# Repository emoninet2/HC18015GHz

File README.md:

# HC18015GHz
-3dB 180 degrees hybrid coupler in 65nm CMOS

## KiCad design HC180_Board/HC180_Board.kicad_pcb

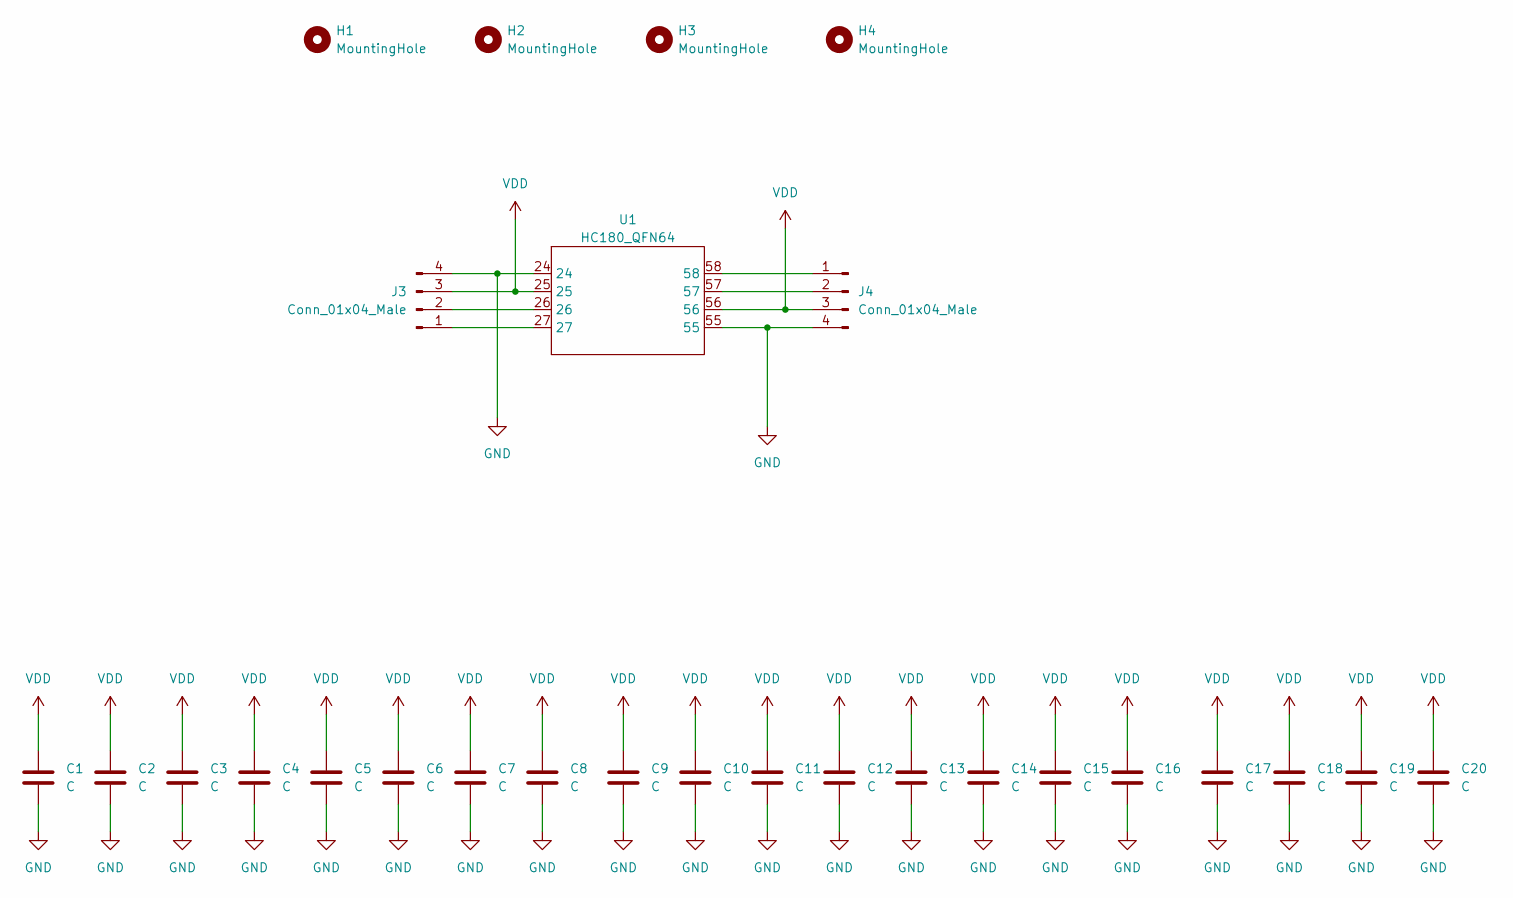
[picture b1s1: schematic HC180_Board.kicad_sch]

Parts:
C1, C2, C3, C4, C5, C6, C7, C8, C9, C10, C11, C12, C13, C14, C15, C16, C17, C18, C19, C20: C; C_0805_2012Metric
H1, H2, H3, H4: MountingHole; MountingHole_5mm_Pad
J3, J4: Conn_01x04_Male; PinHeader_1x04_P2.54mm_Horizontal
U1: HC180_QFN64; QFN-64-1EP_9x9mm_P0.5mm_EP6x6mm

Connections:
GND: C1.2, C2.2, C3.2, C4.2, C5.2, C6.2, C7.2, C8.2, C9.2, C10.2, C11.2, C12.2, C13.2, C14.2, C15.2, C16.2, C17.2, C18.2, C19.2, C20.2, J3.4, J4.4, U1.24, U1.55
unnamed: J3.1, U1.27
unnamed: J3.2, U1.26
unnamed: J4.1, U1.58
unnamed: J4.2, U1.57
VDD: C1.1, C2.1, C3.1, C4.1, C5.1, C6.1, C7.1, C8.1, C9.1, C10.1, C11.1, C12.1, C13.1, C14.1, C15.1, C16.1, C17.1, C18.1, C19.1, C20.1, J3.3, J4.3, U1.25, U1.56

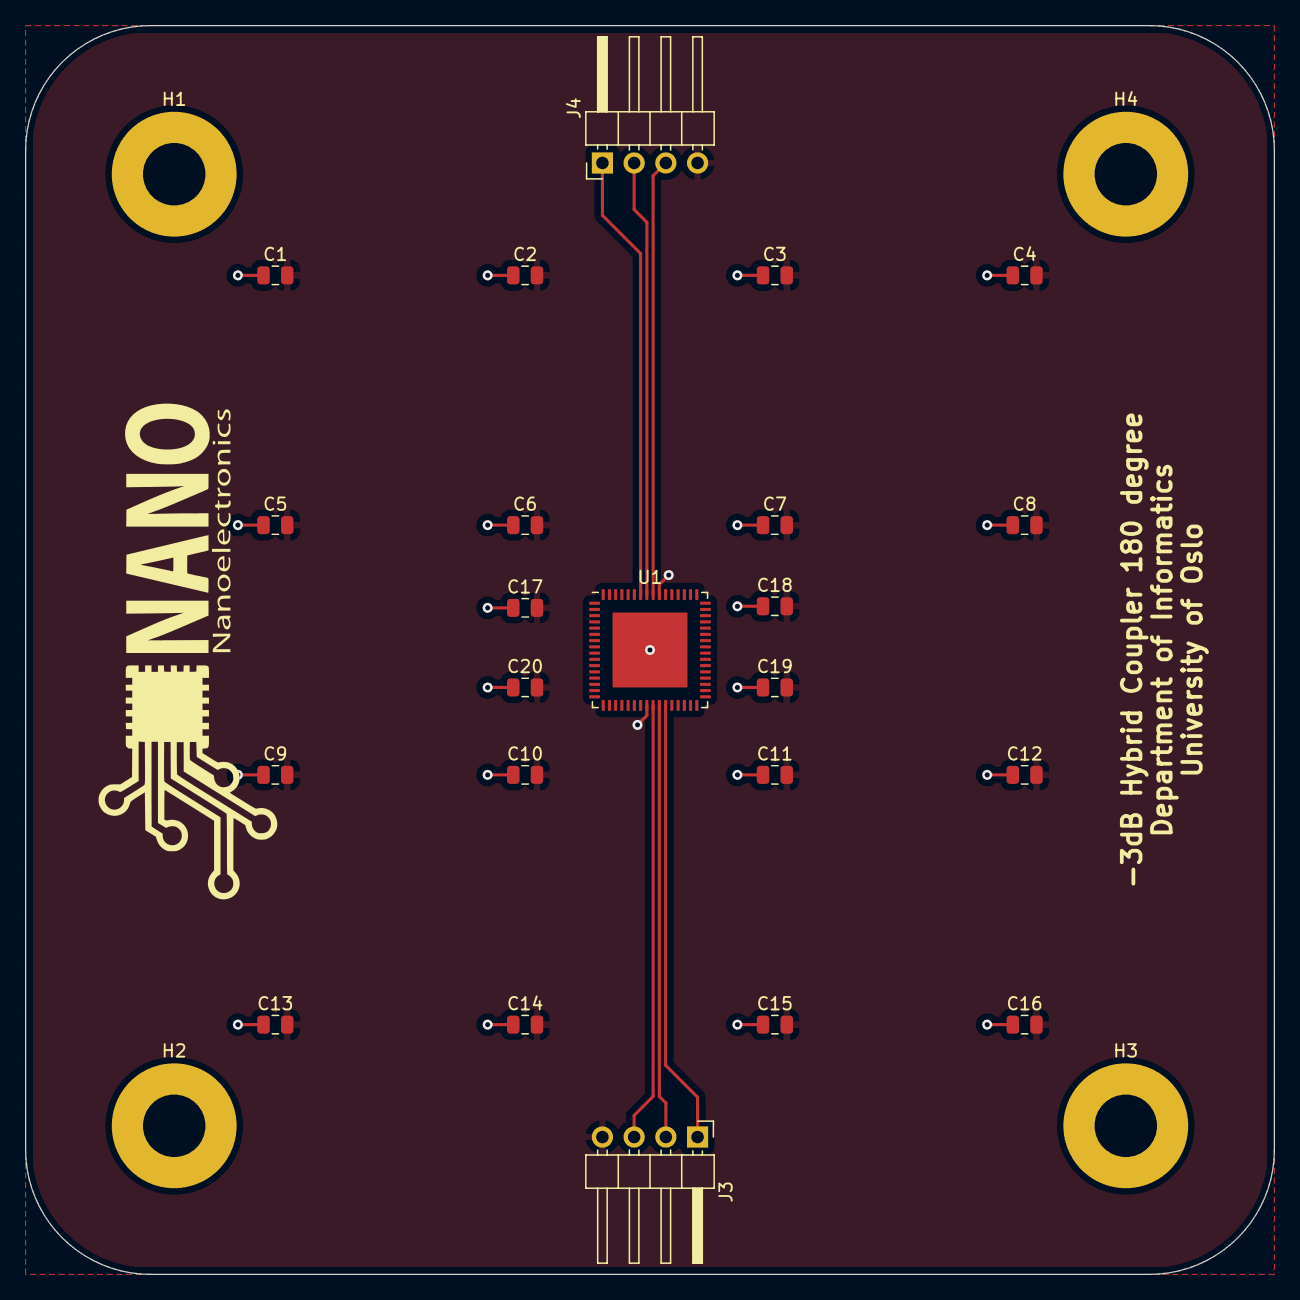
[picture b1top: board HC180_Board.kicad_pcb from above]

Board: 4 copper layers, 100.0 x 100.0 mm, 27 parts (0 on the bottom side), 6 nets.

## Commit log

2022-10-28 added existing project files and folders
2023-06-27 matlab VISA scripts for VNA and DC Power
